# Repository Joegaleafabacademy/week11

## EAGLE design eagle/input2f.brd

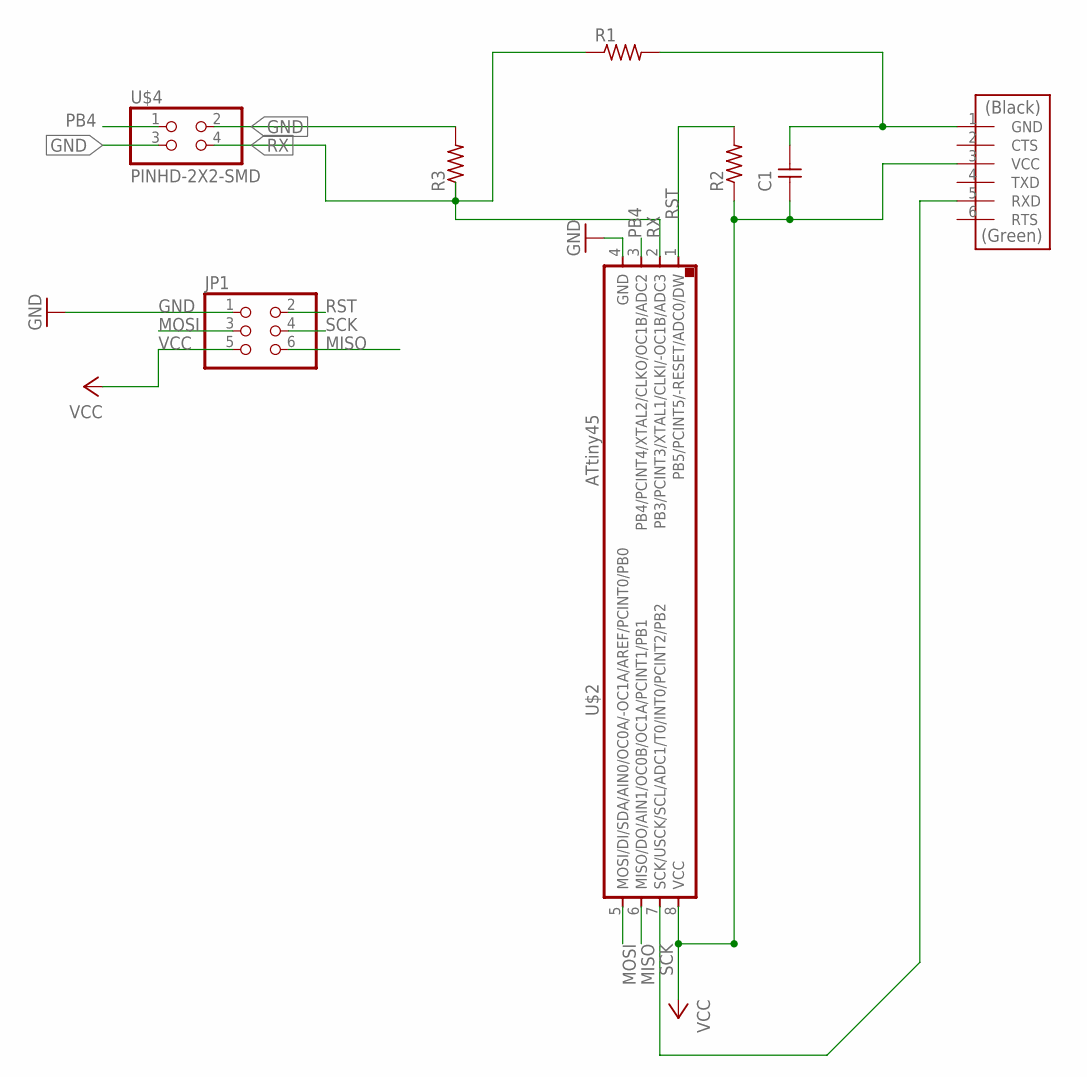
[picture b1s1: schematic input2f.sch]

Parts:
C1: CAP-UNPOLARIZEDFAB; C1206FAB
JP1: PINHD-2X3-SMD; 2X03SMD
R1, R2, R3: RES-US1206FAB; R1206FAB
U$1: FTDI-SMD-HEADER; 1X06SMD
U$2: ATTINY45SI; SOIC8
U$4: PINHD-2X2-SMD; 2X02SMD

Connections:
GND: JP1.1, R3.2, U$2.4 (GND), U$4.2, U$4.3
MISO: JP1.6, U$2.6 (MISO/DO/AIN1/OC0B/OC1A/PCINT1/PB1)
MOSI: JP1.3, U$2.5 (MOSI/DI/SDA/AIN0/OC0A/-OC1A/AREF/PCINT0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)
unnamed: C1.2, R1.2, U$1.1 (GND)
PB4: U$2.3 (PB4/PCINT4/XTAL2/CLKO/OC1B/ADC2), U$4.1
RST: JP1.2, R2.2, U$2.1 (PB5/PCINT5/-RESET/ADC0/DW)
RX: R1.1, R3.1, U$2.2 (PB3/PCINT3/XTAL1/CLKI/-OC1B/ADC3), U$4.4
SCK: JP1.4, U$1.5 (RXD), U$2.7 (SCK/USCK/SCL/ADC1/T0/INT0/PCINT2/PB2)
VCC: C1.1, JP1.5, R2.1, U$1.3 (VCC), U$2.8 (VCC)

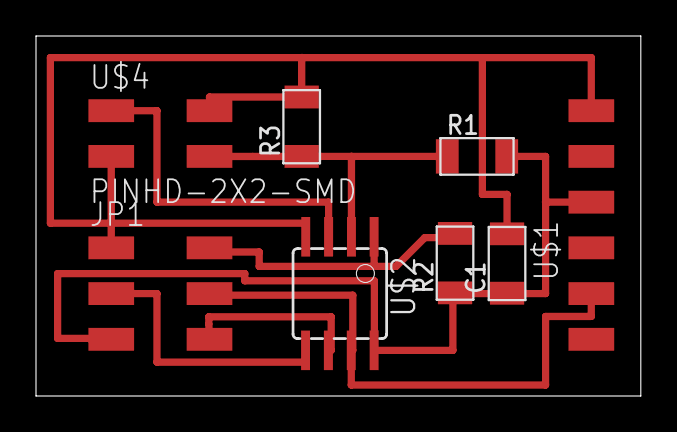
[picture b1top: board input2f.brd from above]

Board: 2 copper layers, 33.6 x 20.0 mm, 8 parts (0 on the bottom side), 9 nets.

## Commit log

2016-07-02 push
